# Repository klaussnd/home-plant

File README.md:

# An automatic watering system for home plants

An open source automatic plant watering system for pot plants in your home.
The system has been employed successfully in my home for several years.
It has a modular design and consists of a measurement module, an irrigation module, and a control module.
A full description as well as some theoretical background can be found [in this paper](http://kschn.users.sf.net/home-plant.pdf).

This repository will contain hardware, firmware, and software utilities.
I am currently in the process of extracting all relevant code from my private repositories.
For now, the repository already contains the hardware.
Code will follow soon.

All circuits and source code are licensed under the terms of the [GNU Affero General Public License](https://www.gnu.org/licenses/agpl-3.0.en.html).

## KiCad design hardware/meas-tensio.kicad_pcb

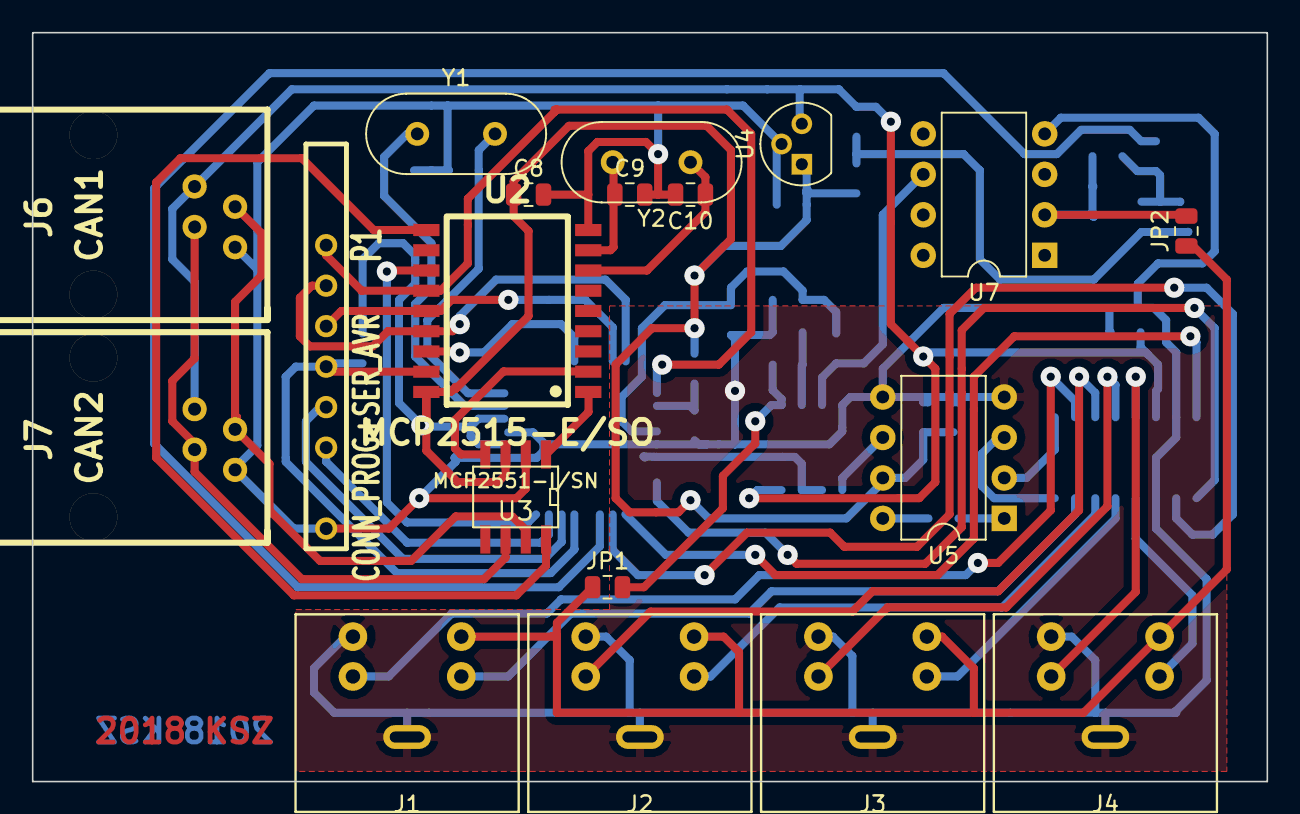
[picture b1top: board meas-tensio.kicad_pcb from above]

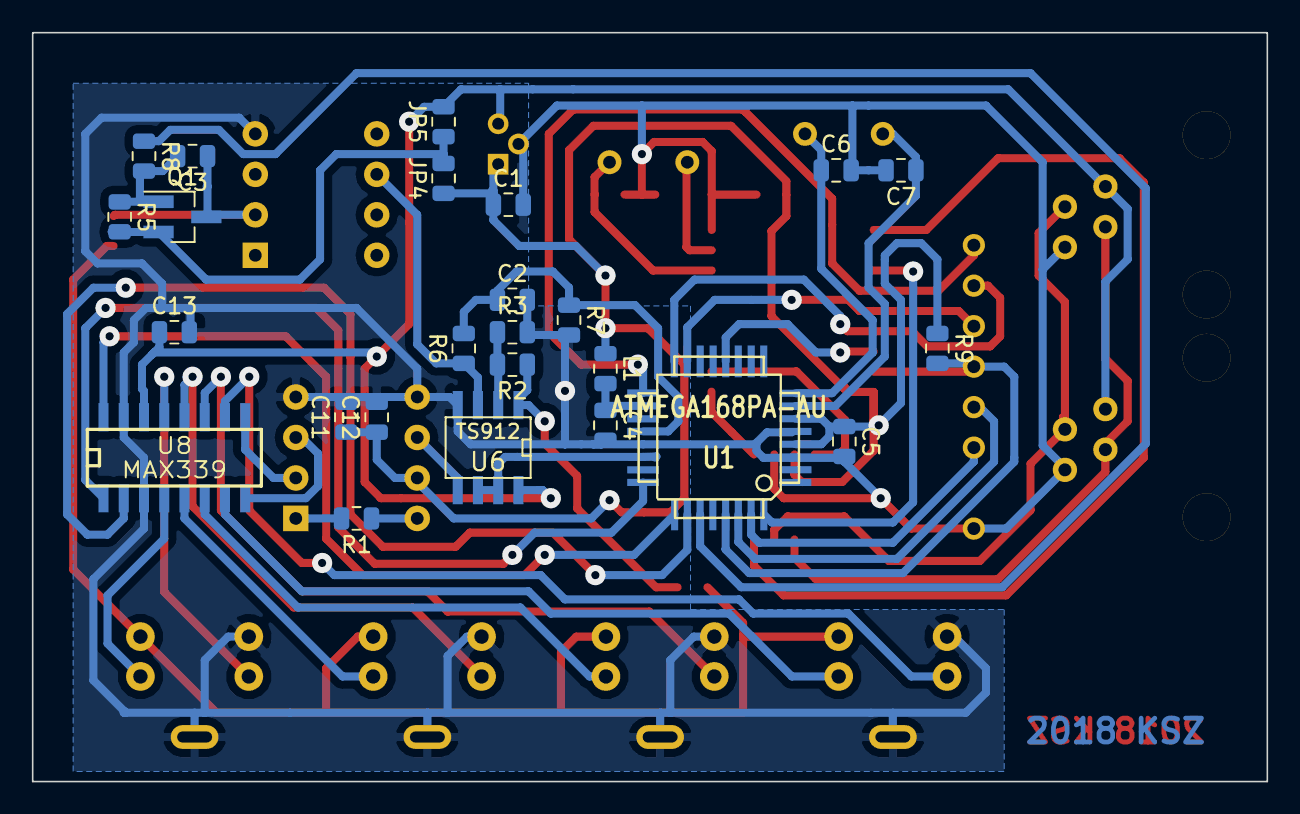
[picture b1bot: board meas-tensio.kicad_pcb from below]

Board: 2 copper layers, 77.5 x 47.0 mm, 44 parts (25 on the bottom side), 47 nets.

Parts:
C1: 4.7u; C_0805_2012Metric
C2, C3, C4, C5, C8, C11: 100n; C_0805_2012Metric
C6, C7: 22p; C_0805_2012Metric
C9, C10: 33p; C_0805_2012Metric
C12: 10u; C_0805_2012Metric
C13: 10n; C_0805_2012Metric
J1: Tens4; CONN_MINI_DIN_4
J2: Tens3; CONN_MINI_DIN_4
J3: Tens2; CONN_MINI_DIN_4
J4: Tens1; CONN_MINI_DIN_4
J6: CAN1; RJ11_RO
J7: CAN2; RJ11_RO
JP1, JP5: a10; R_0805_2012Metric
JP2, JP4: ad; R_0805_2012Metric
L1: 10µ; L_0805_2012Metric
P1: CONN_PROG+SER_AVR; SIL-10_MYAVR+SER
Q1: BSS83P; SOT-23_Handsoldering
R1: 1k; R_0805_2012Metric
R2, R3, R5, R6, R7: 100k; R_0805_2012Metric
R8: 10; R_0805_2012Metric
R9: 10k; R_0805_2012Metric
U1: ATMEGA168PA-AU; TQFP32
U2: MCP2515-E/SO; SOIC18_300
U3: MCP2551-I/SN; SOIC8_150
U4: LP2950-5.0_TO92; TO-92
U5: AD623; DIP-8_W7.62mm
U6: TS912; SOIC8_150
U7: REF02; DIP-8_W7.62mm
U8: MAX339; SOIC16_150
Y1: 7.3728MHz; Crystal_HC49-U_Vertical
Y2: 16MHz; Crystal_HC49-U_Vertical

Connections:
/12V: C13.1, J6.2, J7.2, JP5.2, U4.3, U6.8, U8.14
GNDA: C1.2, C2.2, C4.2, C5.2, C6.2, C7.2, C8.2, C9.2, C10.2, C11.2, C12.2, C13.2, J1.4, J1.5, J2.4, J2.5, J3.4, J3.5, J4.4, J4.5, J6.5, J7.5, P1.10, R3.2, R7.2, U1.3, U1.5, U1.21, U2.9, U3.2, U4.2, U5.4, U5.5, U6.4, U7.4, U8.3, U8.15
unnamed: C2.1, R6.2, R7.1, U1.20
unnamed: C3.1, JP2.2, Q1.3, U7.2
unnamed: C3.2, Q1.1, R5.1, R8.2
unnamed: C4.1, L1.2, U1.18
unnamed: C6.1, U1.8, Y1.2
unnamed: C7.1, U1.7, Y1.1
unnamed: C9.1, U2.8, Y2.2
unnamed: C10.1, U2.7, Y2.1
unnamed: J1.1, U8.7
unnamed: J1.2, U8.10
unnamed: J1.3, J2.3, J3.3, J4.3, JP1.1, JP2.1
unnamed: J2.1, U8.6
unnamed: J2.2, U8.11
unnamed: J3.1, U8.5
unnamed: J3.2, U8.12
unnamed: J4.1, U8.4
unnamed: J4.2, U8.13
unnamed: J6.3, J7.3, U3.7
unnamed: J6.4, J7.4, U3.6
unnamed: JP1.2, R2.1, U6.1
unnamed: JP4.2, JP5.1, Q1.2, R5.2
unnamed: P1.3, U1.17, U2.13
unnamed: P1.4, U1.16, U2.15
unnamed: P1.5, U1.15, U2.14
unnamed: P1.6, R9.2, U1.29, U2.17
unnamed: P1.7, U1.30
unnamed: P1.8, U1.31
unnamed: R1.1, U5.8
unnamed: R1.2, U5.1
unnamed: R2.2, R3.1, U6.2
unnamed: R6.1, U6.3, U7.6
unnamed: R8.1, U1.27
unnamed: U1.12, U2.16
unnamed: U1.22, U6.6, U6.7
unnamed: U1.24, U8.1
unnamed: U1.25, U8.16
unnamed: U1.26, U8.2
unnamed: U1.32, U2.12
unnamed: U2.1, U3.1
unnamed: U2.2, U3.4
unnamed: U2.10, U3.8
unnamed: U5.2, U8.9
unnamed: U5.3, U8.8
unnamed: U5.6, U6.5
VCC: C1.1, C5.1, C8.1, C11.1, C12.1, JP4.1, L1.1, R9.1, U1.4, U1.6, U2.18, U3.3, U4.1, U5.7

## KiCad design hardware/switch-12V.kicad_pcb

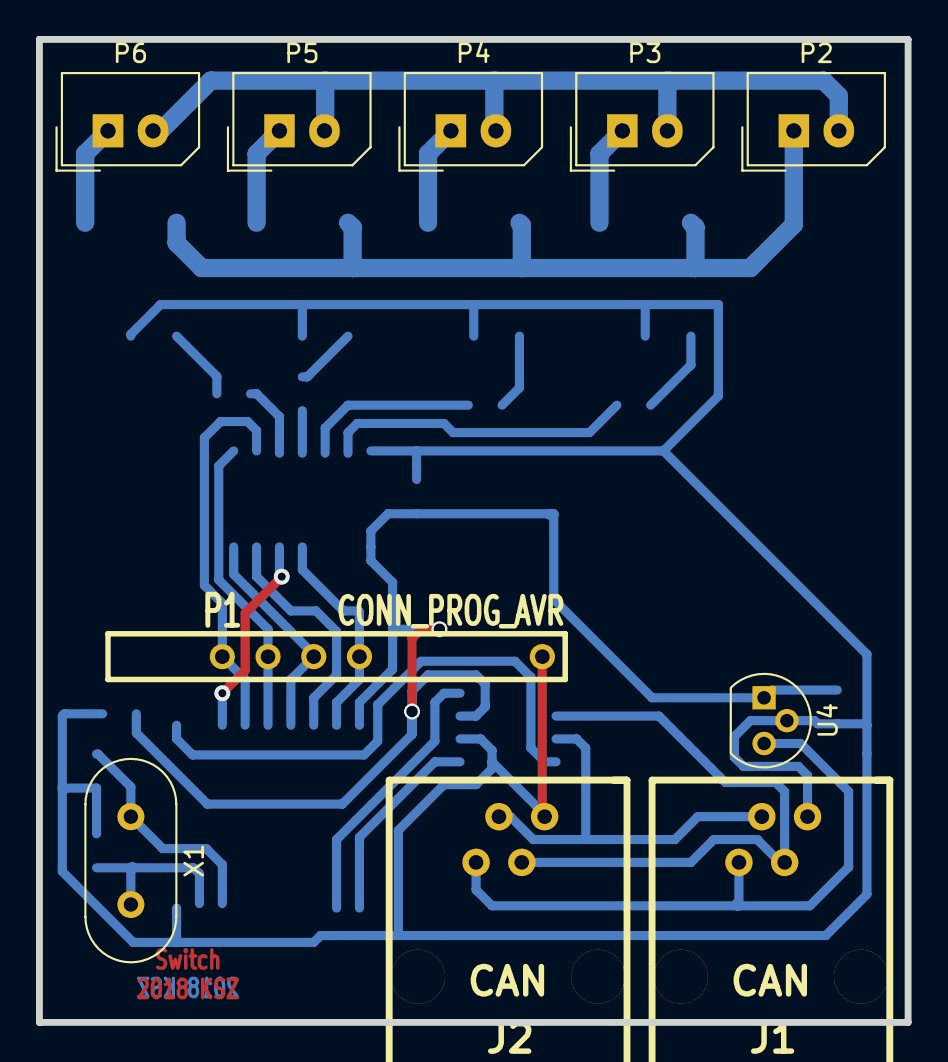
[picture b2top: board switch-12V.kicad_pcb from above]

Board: 2 copper layers, 48.3 x 54.6 mm, 27 parts (0 on the bottom side), 30 nets.

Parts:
C1, C4: 100n; C_0805_2012Metric
C2, C3: 22pF; C_0805_2012Metric
C5: 4.7u; C_0805_2012Metric
J1, J2: CAN; RJ11_RO
P1: CONN_PROG_AVR; SIL-10_MYAVR
P2: 12V; Molex_SPOX_5267-02A_1x02_P2.50mm_Vertical
P3, P4, P5, P6: Pump; Molex_SPOX_5267-02A_1x02_P2.50mm_Vertical
Q1, Q2, Q3, Q4: photoMOS; SOP6
R1: 10k; R_0805_2012Metric
R2, R3, R4, R5: 330; R_0805_2012Metric
U1: ATTINY24; SOIC14_150
U2: MCP2515; SOIC18_300
U3: MCP2551; SOIC8_150
U4: LP2950-5.0_TO92; TO-92
X1: 16MHz; Crystal_HC49-U_Vertical

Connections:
+5V: C1.1, C4.1, C5.1, R1.1, U1.1, U2.18, U3.3, U4.1
/12V+: P2.2, P3.2, P4.2, P5.2, P6.2
/12V-: P2.1, Q1.6, Q2.6, Q3.6, Q4.6
/X1: P3.1, Q1.4
/X2: P4.1, Q2.4
/X3: P5.1, Q3.4
/X4: P6.1, Q4.4
GND: C1.2, C2.1, C3.1, C4.2, C5.2, J1.5, J2.5, P1.10, Q1.2, Q2.2, Q3.2, Q4.2, U1.14, U2.9, U3.2, U4.2
unnamed: C2.2, U2.7, X1.1
unnamed: C3.2, U2.8, X1.2
unnamed: J1.2, J2.2, U4.3
unnamed: J1.3, J2.3, U3.7
unnamed: J1.4, J2.4, U3.6
unnamed: P1.3, U1.9, U2.13
unnamed: P1.4, U1.8, U2.14
unnamed: P1.5, U1.7, U2.15
unnamed: P1.6, R1.2, U1.4, U2.17
unnamed: Q1.1, R2.1
unnamed: Q2.1, R3.1
unnamed: Q3.1, R4.1
unnamed: Q4.1, R5.1
unnamed: R2.2, U1.13
unnamed: R3.2, U1.12
unnamed: R4.2, U1.11
unnamed: R5.2, U1.10
unnamed: U1.5, U2.12
unnamed: U1.6, U2.16
unnamed: U2.1, U3.1
unnamed: U2.2, U3.4
unnamed: U2.10, U3.8

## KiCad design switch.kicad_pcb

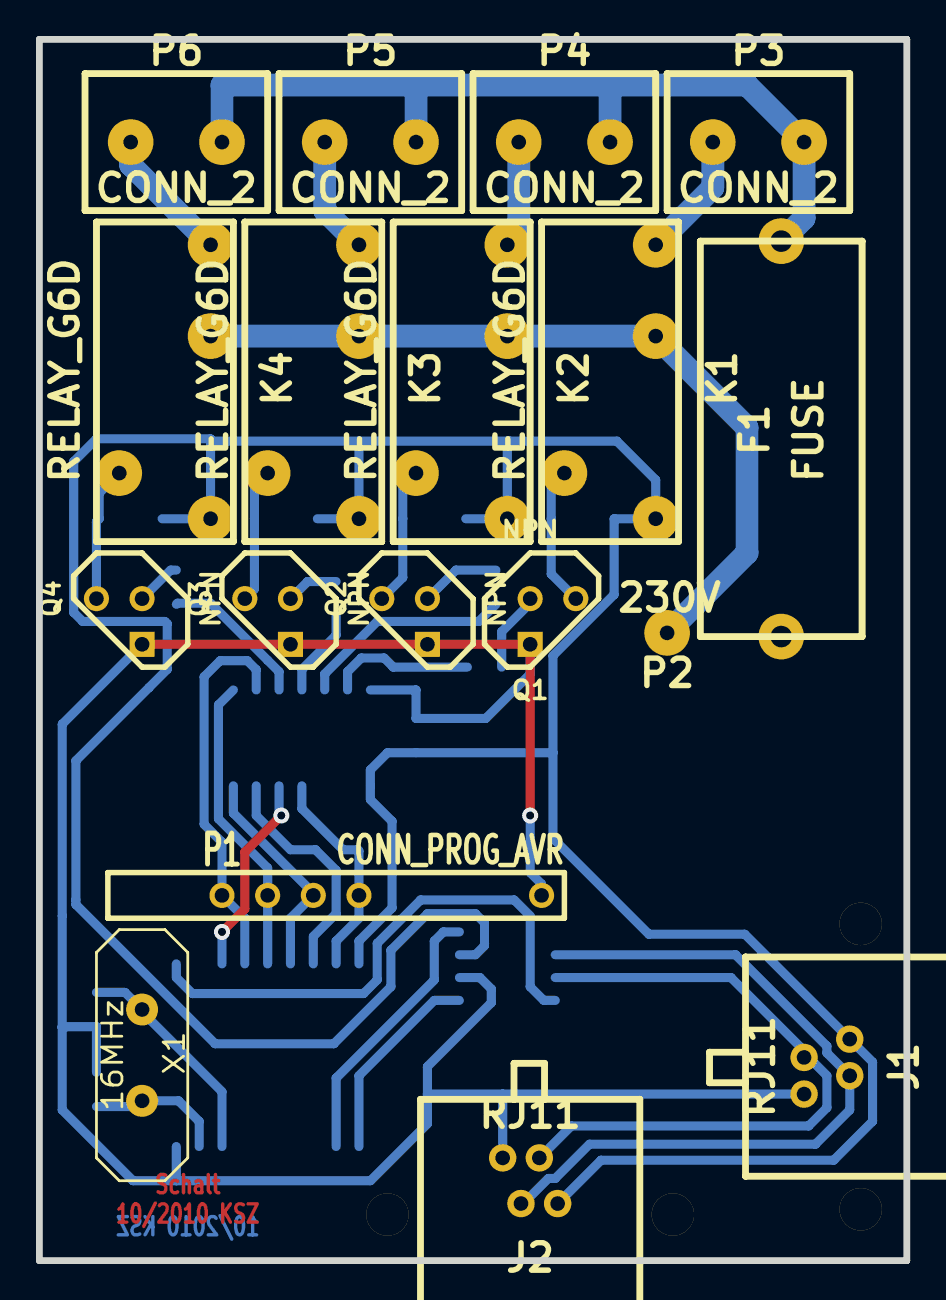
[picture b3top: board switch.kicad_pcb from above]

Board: 2 copper layers, 48.3 x 67.9 mm, 33 parts (0 on the bottom side), 33 nets.

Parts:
C1: 100n; SM0805
C2, C3: 22pF; SM0805
D1, D2, D3, D4: DIODE; Diode-MiniMELF_Standard_RevA_27July2010
F1: FUSE; FUSE_PRINT
IC1: ATTINY24; SOIC14_150
IC2: MCP2515; SOIC18_300
IC3: MCP2551; SOIC8_150
J1, J2: RJ11; RJ11_RN
K1, K2, K3, K4: RELAY_G6D
P1: CONN_PROG_AVR; SIL-10_MYAVR
P2: 230V; PAD
P3, P4, P5, P6: CONN_2; CONN_AKL2
Q1: NPN; TO92-INVERT
Q2, Q3, Q4: NPN; TO92
R1: 10k; SM0805
R2, R3, R4, R5: 15k; SM0805
X1: 16MHz; HC-18UV

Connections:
+5V: C1.1, D1.2, D2.2, D3.2, D4.2, IC1.1, IC2.18, IC3.3, J1.2, J2.2, K1.1, K2.1, K3.1, K4.1, R1.1
/230V+: F1.2, P3.2, P4.2, P5.2, P6.2
/230V-: K1.5, K2.5, K3.5, K4.5, P2.1
/X1: K1.7, P3.1
/X2: K2.7, P4.1
/X3: K3.7, P5.1
/X4: K4.7, P6.1
GND: C1.2, C2.1, C3.1, IC1.14, IC2.9, IC3.2, J1.5, J2.5, P1.10, Q1.1, Q2.1, Q3.1, Q4.1
unnamed: IC2.10, IC3.8
unnamed: IC2.2, IC3.4
unnamed: IC2.1, IC3.1
unnamed: IC1.6, IC2.16
unnamed: IC1.9, IC2.13, P1.3
unnamed: IC1.5, IC2.12
unnamed: C2.2, IC2.7, X1.1
unnamed: IC3.6, J1.4, J2.4
unnamed: IC1.8, IC2.14, P1.4
unnamed: Q3.2, R4.1
unnamed: Q4.2, R5.1
unnamed: IC1.10, R5.2
unnamed: IC1.11, R4.2
unnamed: D1.1, K1.13, Q1.3
unnamed: D2.1, K2.13, Q2.3
unnamed: D3.1, K3.13, Q3.3
unnamed: D4.1, K4.13, Q4.3
unnamed: Q1.2, R2.1
unnamed: IC1.13, R2.2
unnamed: Q2.2, R3.1
unnamed: IC1.12, R3.2
unnamed: IC3.7, J1.3, J2.3
unnamed: C3.2, IC2.8, X1.2
unnamed: IC1.7, IC2.15, P1.5
unnamed: IC1.4, IC2.17, P1.6, R1.2

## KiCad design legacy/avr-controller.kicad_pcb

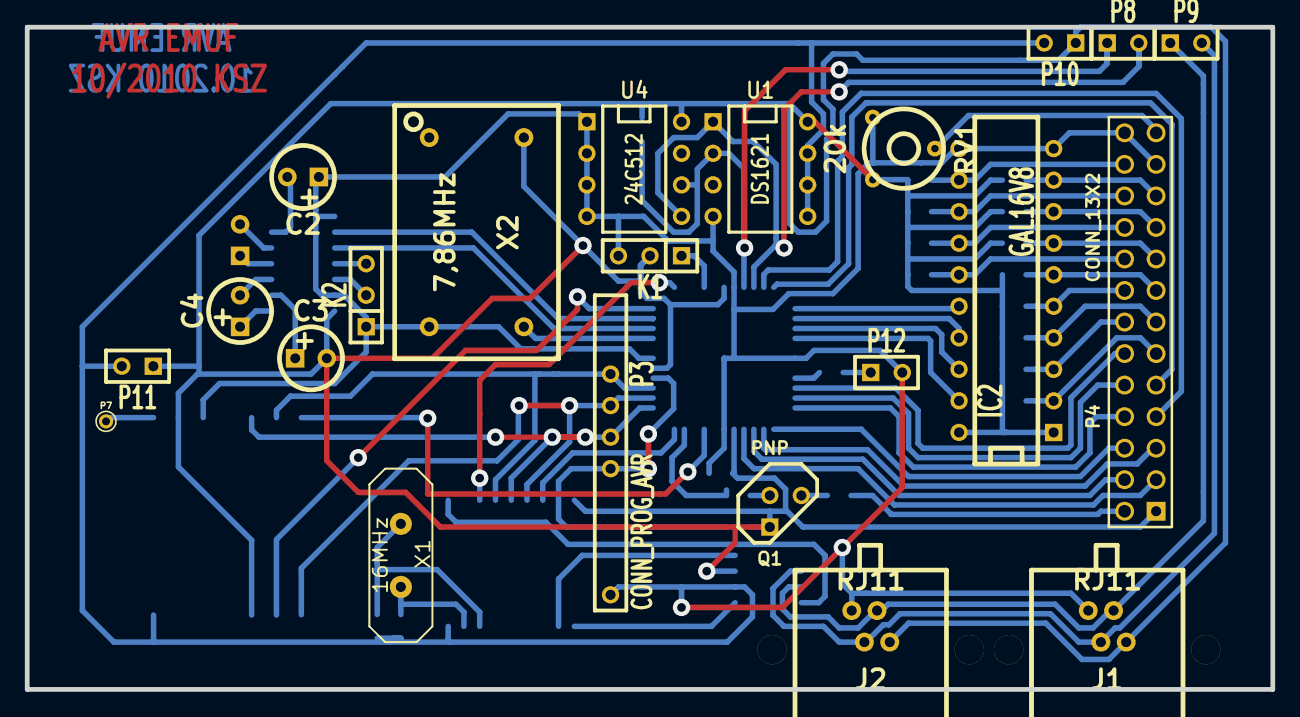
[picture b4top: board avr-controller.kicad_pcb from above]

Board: 2 copper layers, 100.3 x 53.3 mm, 49 parts (0 on the bottom side), 64 nets.

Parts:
C1: 100n; SM0805
C2, C3, C4, C5: 1; Elko_vert_DM5_RM2-5
C6, C7: 22pF; SM0805
IC1: ATMEGA32-A; TQFP44
IC2: GAL16V8; DIP-20__300
IC3: MCP2515; SOIC18
IC4: MCP2551; SOIC8_150
J1, J2: RJ11; RJ11_RN
K1, K2: CONN_3; SIL-3
P3: CONN_PROG_AVR; SIL-10_MYAVR
P4: CONN_13X2; pin_array_13x2
P7: ANT; PINTST
P8: i2c; SIL-2
P9: CAN; SIL-2
P10, P11: VCC; SIL-2
P12: LED; SIL-2
Q1: PNP; TO92-INVERT
R1, R2, R3, R4: 10k; SM0805
R5, R6, R7, R9, R10, R11, R12, R13, R14, R15, R16, R17: 100k; SM0805
R8: 33; SM0805
R18: 240; SM0805
RV1: 20k; POT-PT6
U1: DS1621; DIP-8__300
U2: MAX232; SOIC16_150
U3: RFM12
U4: 24C512; DIP-8__300
X1: 16MHz; HC-18UV
X2: 7,86MHz; OSCIL

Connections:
+5V: C1.1, C3.2, IC1.5, IC1.17, IC1.38, IC2.1, IC2.20, IC3.18, IC4.3, J1.2, J2.2, K1.2, P4.1, P10.1, P11.1, Q1.1, R1.1, R3.1, R4.1, R5.1, R6.1, R7.1, R9.1, R10.1, R11.1, R12.1, R13.1, R14.1, R15.1, R16.1, R17.1, RV1.3, U1.8, U2.16, U3.3, U3.9, U4.8, X2.14
GND: C1.2, C2.1, C6.1, C7.1, IC1.6, IC1.18, IC1.28, IC1.39, IC2.10, IC2.11, IC3.9, IC4.2, J1.5, J2.5, K1.3, K2.1, P3.10, P4.23, P4.26, P10.2, P11.2, P12.2, RV1.1, U1.4, U1.5, U1.6, U1.7, U2.10, U2.15, U3.7, U3.10, U4.1, U4.2, U4.3, U4.4, X2.7
unnamed: IC3.1, IC4.1
unnamed: IC4.7, J1.3, J2.3, P9.1
unnamed: IC3.2, IC4.4
unnamed: IC1.41, U3.14
unnamed: C7.2, IC3.7, X1.1
unnamed: C5.1, U2.4
unnamed: C5.2, U2.5
unnamed: C4.1, U2.1
unnamed: C4.2, U2.3
unnamed: C3.1, U2.2
unnamed: C2.2, U2.6
unnamed: IC1.36, P4.4
unnamed: IC1.22, P4.9
unnamed: C6.2, IC3.8, X1.2
unnamed: IC3.10, IC4.8
unnamed: IC1.12, IC3.12
unnamed: IC1.3, IC3.13, P3.3, U3.13
unnamed: IC1.1, IC3.14, P3.5, U3.12
unnamed: IC1.2, IC3.15, P3.4, U3.1
unnamed: IC1.44, IC3.16
unnamed: IC1.4, IC3.17, P3.6, R1.2
unnamed: K2.2, U2.14
unnamed: P12.1, R18.1
unnamed: IC1.30, R18.2
unnamed: IC4.6, J1.4, J2.4, P9.2
unnamed: Q1.2, R2.2
unnamed: Q1.3, R8.1
unnamed: P7.1, U3.8
unnamed: IC1.20, P8.2, R3.2, U1.1, U4.5
unnamed: IC1.8, X2.8
unnamed: IC1.9, U2.12
unnamed: IC1.11, U3.2
unnamed: IC1.21, P4.7
unnamed: IC2.3, P4.14, R16.2
unnamed: IC2.6, P4.15, R13.2
unnamed: IC2.9, P4.21, R10.2
unnamed: IC1.23, IC2.16
unnamed: IC1.10, U2.11
unnamed: K2.3, U2.13
unnamed: IC1.33, P4.8
unnamed: IC1.43, R2.1
unnamed: IC1.24, IC2.17
unnamed: IC1.25, IC2.18
unnamed: IC1.35, P4.5
unnamed: IC1.26, IC2.19
unnamed: IC1.37, P4.3
unnamed: IC1.15, K1.1
unnamed: P4.2, R8.2
unnamed: IC1.31, P4.12
unnamed: IC2.12, P4.24, R5.2
unnamed: P4.25, RV1.2
unnamed: IC2.15, P4.18, R9.2
unnamed: IC2.13, P4.22, R6.2
unnamed: IC2.2, P4.11, R17.2
unnamed: IC2.5, P4.16, R14.2
unnamed: IC2.8, P4.19, R11.2
unnamed: IC2.4, P4.13, R15.2
unnamed: IC2.7, P4.17, R12.2
unnamed: IC1.34, P4.6
unnamed: IC1.32, P4.10
unnamed: IC1.19, P8.1, R4.2, U1.2, U4.6
unnamed: IC2.14, P4.20, R7.2

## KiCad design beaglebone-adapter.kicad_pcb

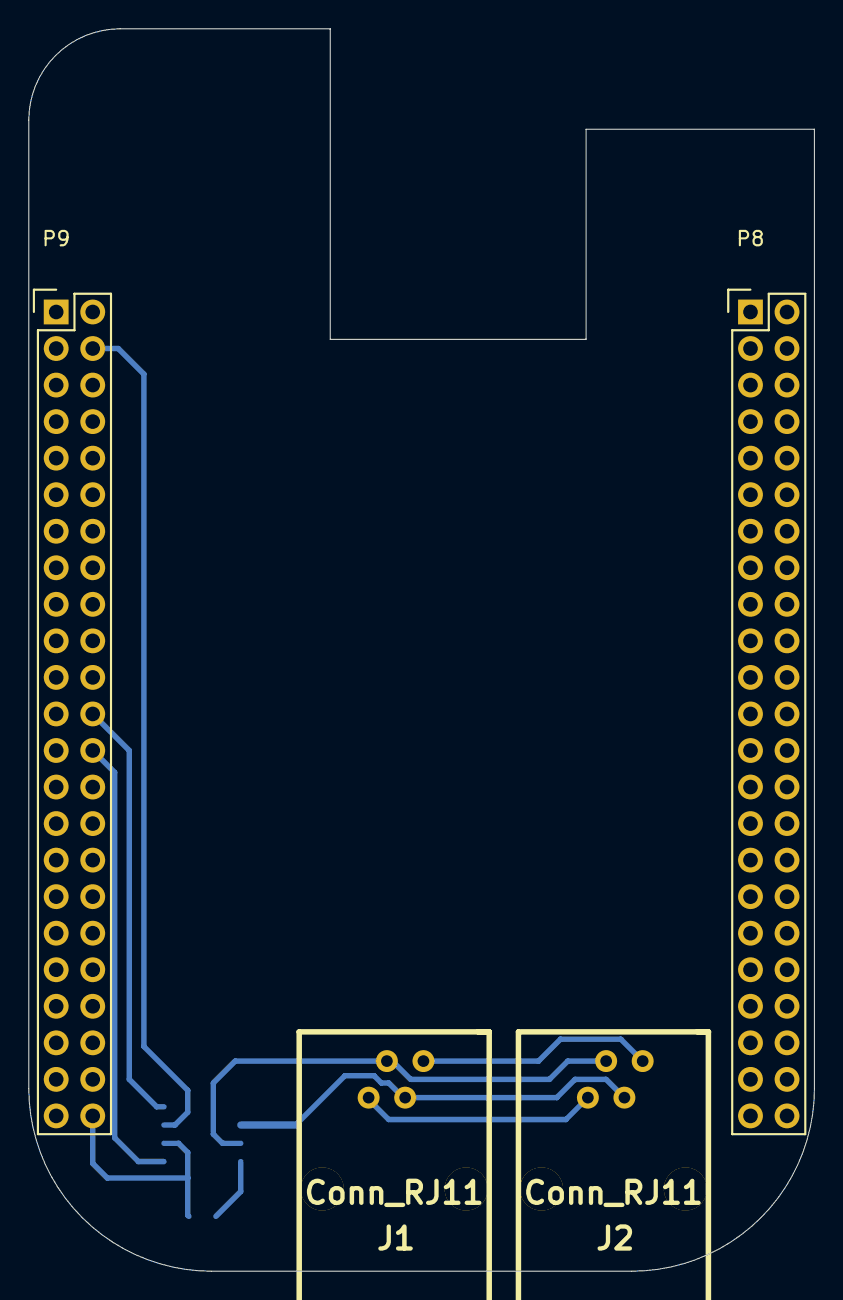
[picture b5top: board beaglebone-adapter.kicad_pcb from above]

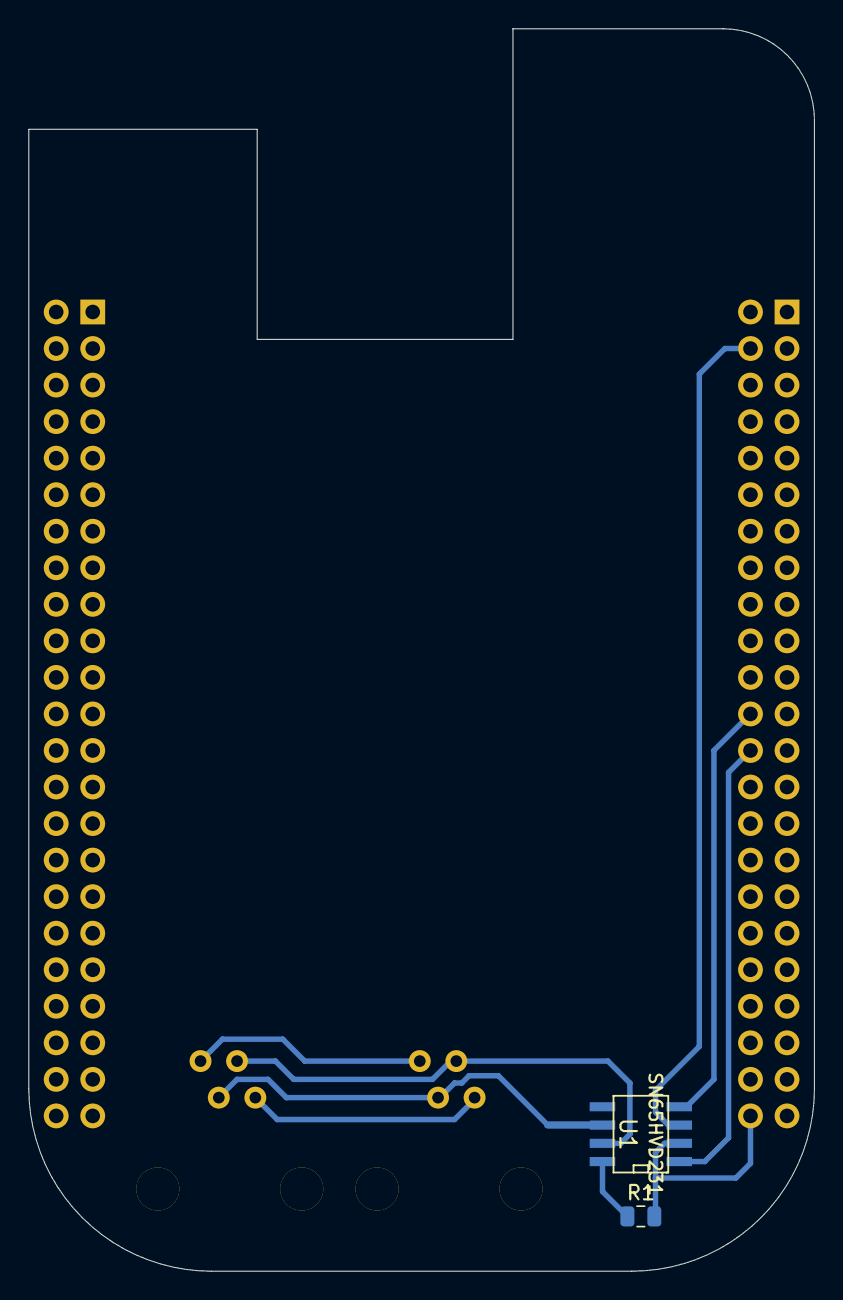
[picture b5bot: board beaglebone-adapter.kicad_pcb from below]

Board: 2 copper layers, 54.6 x 86.4 mm, 6 parts (2 on the bottom side), 10 nets.

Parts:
J1, J2: Conn_RJ11; RJ11_RO
P8, P9: BeagleBone_Black_Header; Socket_BeagleBone_Black
R1: 10k; R_0805_2012Metric
U1: SN65HVD231; SOIC8_150

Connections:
+3V3: P9.3, P9.4, U1.3
+5V: P9.5, P9.6
GNDD: P8.1, P8.2, P9.1, P9.2, P9.43, P9.44, P9.45, P9.46, R1.2, U1.2
unnamed: J1.2, J2.2
unnamed: J1.3, J2.3, U1.7
unnamed: J1.4, J2.4, U1.6
unnamed: J1.5, J2.5
unnamed: P9.24, U1.4
unnamed: P9.26, U1.1
unnamed: R1.1, U1.8

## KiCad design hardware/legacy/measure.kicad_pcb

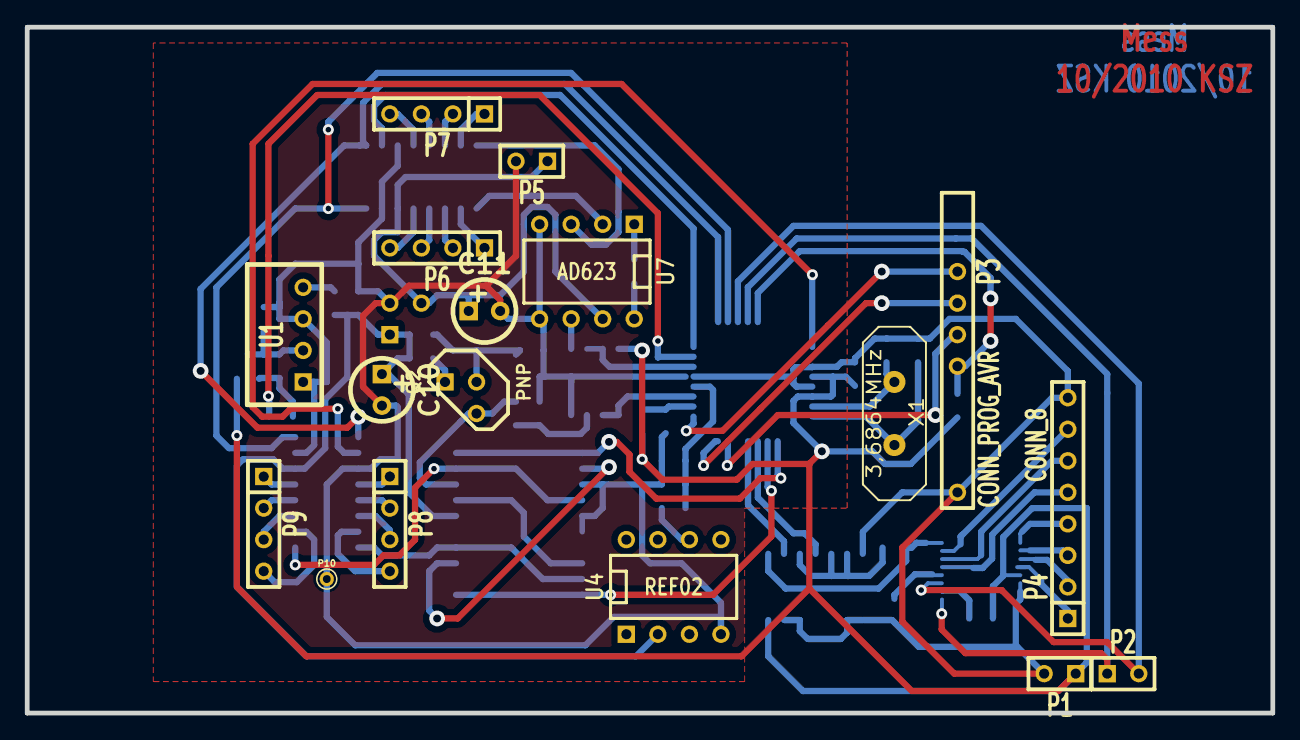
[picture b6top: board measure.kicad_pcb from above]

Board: 2 copper layers, 100.3 x 55.2 mm, 49 parts (0 on the bottom side), 69 nets.

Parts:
C1, C2: 0,1µF; SM0805
C3, C4, C5, C7: 100nF; SM0805
C6, C8: 22pF; SM0805
C9: 220pF; SM0805
C10: 0,33µF; Elko_vert_DM5_RM2-5
C11: 0,1µF; Elko_vert_DM5_RM2-5
IC1: ATMEGA8-AI; TQFP32
L1, L2: 10µH; SM0805
P1: VCC; SIL-2
P2: I2C; SIL-2
P3: CONN_PROG_AVR; SIL-10_MYAVR
P4: CONN_8; SIL-8
P5: CONN_2; SIL-2
P6, P7, P8, P9: CONN_4; SIL-4
P10: CONN_1; PINTST
Q1: MOSFET_P; SOT23GDS
Q2: PNP; TO92-INVERT
R1, R7: 1k; SM0805
R2, R8: 1M; SM0805
R3, R4: 10k; SM0805
R9: 100k; SM0805
R10: 2,8k; SM0805
R11: 4,7k; SM0805
R12: 47k; SM0805
R13, R14: 20k; SM0805
U1: SIM1; SIL-4_SIM
U2: 4011; SOIC14_150
U3: ADG728; TSSOP16
U4: REF02; DIP-8__300
U5: TS912; SOIC8_150
U6: 78L10; TO92
U7: AD623; DIP-8__300
U9: MAX333A; SOIC20_300
U10, U11: MAX339; SOIC16_150
X1: 3,6864MHz; HC-18UV

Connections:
+5V: C3.1, IC1.4, IC1.6, L1.1, P1.1, Q1.S, R3.1, R4.1, U2.14, U3.13, U5.8
+24V: C7.2, C10.1, L2.2, R10.1, R11.1, U4.2, U6.1, U9.16, U10.14
/t1: R2.1, U2.1, U3.8
/t4: IC1.28, P2.1, U3.1
/t5: IC1.27, P2.2, U3.3
/t6: R4.2, U3.2
/t8: C9.2, U3.4
/t9: P4.5, U3.5
/t10: P4.6, U3.6
/t11: P4.7, U3.7
/t12: P4.1, U3.12
/t13: P4.2, U3.11
/t14: P4.3, U3.10
/t15: P4.4, U3.9
AGND: C2.1, C3.2, C4.2, C5.2, C6.2, C7.1, C8.2, C9.1, C10.2, C11.2, IC1.3, IC1.5, IC1.21, P1.2, P3.10, P4.8, P5.2, P10.1, R9.2, R12.2, R14.2, U1.1, U1.3, U2.7, U2.8, U2.9, U2.12, U2.13, U3.14, U3.15, U3.16, U4.4, U5.4, U6.2, U7.4, U7.5, U9.3, U9.5, U9.6, U10.3, U10.15, U11.3, U11.15
unnamed: R13.1, U4.6
unnamed: U9.9, U9.14, U10.8
unnamed: P6.2, U11.11
unnamed: P6.3, U11.12
unnamed: P6.4, U11.13
unnamed: IC1.25, U10.1, U11.1
unnamed: P7.4, U11.4
unnamed: P7.3, U11.5
unnamed: P7.2, U11.6
unnamed: P9.2, U10.12
unnamed: P9.3, U10.11
unnamed: P9.4, U10.10
unnamed: P8.1, U10.4
unnamed: P8.2, U10.5
unnamed: P8.3, U10.6
unnamed: P8.4, U10.7
unnamed: P7.1, U11.7
unnamed: P6.1, U11.10
unnamed: U5.5, U7.6
unnamed: C1.2, Q1.G, R1.2
unnamed: C1.1, C2.2, Q1.D, U1.2
unnamed: IC1.15, P3.5
unnamed: C8.1, IC1.8, X1.2
unnamed: C6.1, IC1.7, X1.1
unnamed: U7.2, U11.9
unnamed: U7.3, U11.8
unnamed: R7.2, U7.8
unnamed: R2.2, U2.3, U2.5, U2.6
unnamed: IC1.12, U2.4
unnamed: IC1.23, R1.1
unnamed: IC1.24, U11.2
unnamed: IC1.16, P3.4
unnamed: IC1.26, U10.16, U11.16
unnamed: IC1.17, P3.3
unnamed: IC1.19, U5.1, U5.2
unnamed: IC1.29, P3.6, R3.2
unnamed: C4.1, IC1.18, L1.2
unnamed: IC1.1, U10.2
unnamed: P9.1, U10.13
unnamed: U9.2, U9.13
unnamed: Q2.1, R10.2
unnamed: Q2.2, R11.2, R12.1
unnamed: R8.2, R9.1, U5.3
unnamed: Q2.3, R8.1, U9.18
unnamed: R7.1, U7.1
unnamed: IC1.10, U9.1, U9.20
unnamed: U9.8, U9.17
unnamed: L2.1, U1.4
unnamed: U9.4, U9.19, U10.9
unnamed: C5.1, IC1.20, R13.2, R14.1
unnamed: IC1.22, U5.6, U5.7
unnamed: IC1.11, U9.10, U9.11
unnamed: IC1.13, U2.2
unnamed: C11.1, P5.1, U6.3, U7.7, U11.14

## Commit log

2018-10-20 Added boards
2018-10-20 added net lists for giess project
2018-10-20 Convert measurement schematics to new kicad version
2018-10-20 board giess-schalt improved
2018-10-20 projekt: avr-emuf & giess-mess boards layout improved
2018-10-20 imrpoved schematics/boards
2018-10-20 board giess-schalt adjusted for Reichelt's new RJ12 connectors
2018-10-20 Update switching module schematic to new KiCad version
2018-10-20 Fix ground of instrument amplifier
2018-10-20 Update annotation
2018-10-20 Update switching module
2018-10-20 Move measurement module v1 into legacy folder
2018-10-20 Improve tensiometer module.
    Also allow changing tensiometer supply voltage variant with jumpers / non-soldered resistors.
2018-10-20 Vcc of instrumentation amplifier is 5V instead of 12V
2018-10-20 Add tensiometer measurement module
2018-10-20 Add tensiometer board
2018-10-20 Fix edge
2018-10-20 Fix tensiometer schematic
2018-10-20 Change capacitor value in water content and switching modules
2018-10-20 Change select pin
2018-10-20 Improve analogue part
2018-10-20 Move all plugs onto one side of the PCB
2018-10-20 Connect Vcc and GND from CAN interface
2018-10-20 Convert switching module PCB to new KiCad format
2018-10-20 Use Mini-DIN plug
2018-10-20 Update capacitive water content module to new kicad version 5
2018-10-20 Convert board into new KiCad format
2018-10-20 Make schematics up to date
2018-10-20 Convert switching module to new KiCad version 5
2018-10-20 Adjust edge, add text
2018-10-20 Adjust tensiometer module for 12V supply voltage
2018-10-20 Add simple RJ11 connector symbol and use it
2018-10-20 Water content capacity board
2018-10-20 Add measurement module for capacitive soil water probe Giesomat
2018-10-20 Update tensiometer schematic to newest kicad version 5
2018-10-20 Add 5V regulator to capacity measurement module
2018-10-20 Rename switching module
2019-07-14 Add CAN adapter for beagle bone
2019-07-14 Update footprint from module. Fix pad connection to ground plane.
2019-07-14 Fix relay wiring of 12V switch board
2019-07-14 Add submodule for kicad libraries and modules
2019-07-14 Rename switching board
2019-07-14 Move AVR controller to legacy folder
2019-07-14 Add pro file
2019-07-14 Convert to new KiCad format
2019-07-14 Fix conflicting capacitor placement
2019-07-14 Connect screen of Mini-DIN plug to GND
2019-07-14 Remove unnecessary jumper. Remove ground loop.
2019-07-14 Move hardware into sub-folder
2019-07-14 Correct capacitor value
2019-07-14 Add 12V version of switching module
2019-07-14 Update kicad submodule
2019-07-14 Add readme
2019-07-21 Improve silk
2019-08-09 Improve label position
2025-04-21 Change capacitor value in switching modules
2025-04-21 Add firmware for tensiometer module
